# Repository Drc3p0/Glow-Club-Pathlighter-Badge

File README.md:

<div id="top"></div>

<br />
<div align="center">

<h3 align="center">Glow Club Pathlighter Badge</h3>

  <p align="center">
    wearable PCB art for the community
  
  </p>
</div>

<!-- ABOUT THE PROJECT -->
## About The Project
This PCB was created as a workshop aid to teach people about LEDs and soldering, and as a way to demistify the process of importing custom art layers into Kicad.  The PCB is intended to be worn on a lanyard, as a way to keep us all glowing safely at night. It was debuted at SOAK '22 for the There U Glow electronics education camp, used for a soldering workshop for ToorCamp 2022 participants, and at Chaos Communication Camp '23. 

### Created With

* [Procreate](https://procreate.art/)
* [Affinity Designer](https://affinity.serif.com/)
* [Kicad 6.0](https://kicad.org/)
* [OshPark](https://oshpark.com/)

The designs are free to be modified however you'd like.  

<div align="center">
  
</div>

### Build it! 

Components are easy to source and assemble, and consist of a [generic AAA single battery holder x2](https://www.mouser.com/ProductDetail/12BH412-GR), your favorite 5mm LEDs (we like these [color changing ones](https://www.amazon.com/Multicolor-Flashing-Changing-Electronics-Components/dp/B01C19END2/ref=sr_1_13?crid=3ENC4HC6ILEX9&keywords=slow+flash+led+5mm&qid=1654971525&sprefix=slow+flash+led+5mm%2Caps%2C144&sr=8-13)), and this
[tiny SPDT switch](https://www.mouser.com/ProductDetail/642-MHSS1105) to conserve your battery power.

## Contributing

Contributions are what make the open source community such an amazing place to learn, inspire, and create. Any contributions you make are **greatly appreciated**.

If you have a suggestion that would make this better, please fork the repo and create a pull request. You can also simply open an issue with the tag "enhancement".
Don't forget to give the project a star! Thanks again!

1. Fork the Project
2. Create your Feature Branch (`git checkout -b feature/AmazingFeature`)
3. Commit your Changes (`git commit -m 'Add some AmazingFeature'`)
4. Push to the Branch (`git push origin feature/AmazingFeature`)
5. Open a Pull Request

## License

Distributed under the CERN Open Hardware License (CERN-OHL-W). See `LICENSE.txt` for more information.

## Contact

For inquiries, email me @ [GlowClub@DarcyNeal.com](mailto:glowclub@darcyneal.com)

Project Link: [https://github.com/Drc3p0/Glowbug-Club-PCB](https://github.com/Drc3p0/Glow-Club-Pathlighter-Badge)

<!-- ACKNOWLEDGMENTS -->
## Acknowledgments
Thanks to:
* [OshPark](https://oshpark.org) for providing the PCBs for this community project
* the elusive Josh for providing power consumption data
* there U glow camp @ [SOAK](https://soakpdx.com/) for helping distribute these boards & [teach folks about LEDs](https://docs.google.com/document/d/180WD4LogMjx8FmKcFc0dmlTEKJ1Xa7dIHlEhSLMOAxA/edit?usp=sharing)
* [Toorcamp 2022](https://talks.toorcon.net/toorcamp-2020-2019/talk/DNWBQS/).  Over 75 students were able to assemble badges during the ~2 hr workshop.
* [Chaos Communication Camp '23 and the Hardware Hacking Village](https://events.ccc.de/camp/2023/hub/camp23/en/event/solder-a-pathlighter-pcb-badge-day-1/).  Over 160 students completed their badges over two workshops, each ~1.5hrs. 
<p align="right">(<a href="#top">back to top</a>)</p>

To date, the Glow Club now has over 450 members! May we all shine a little brighter as a result. :)

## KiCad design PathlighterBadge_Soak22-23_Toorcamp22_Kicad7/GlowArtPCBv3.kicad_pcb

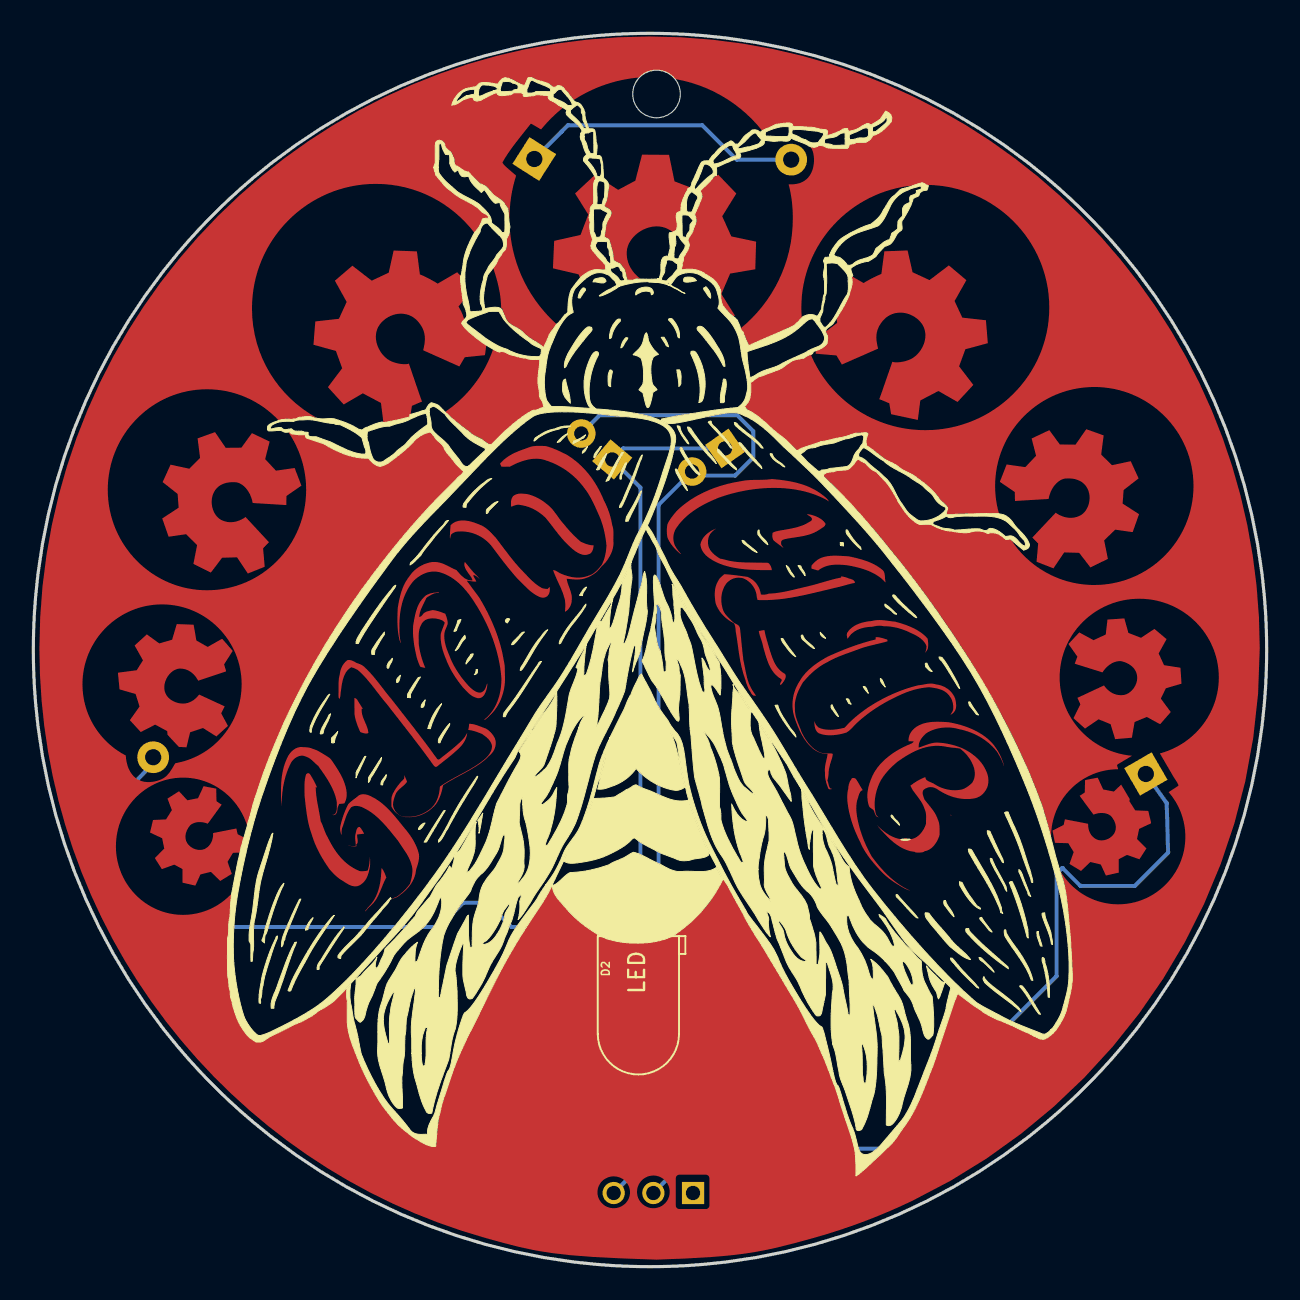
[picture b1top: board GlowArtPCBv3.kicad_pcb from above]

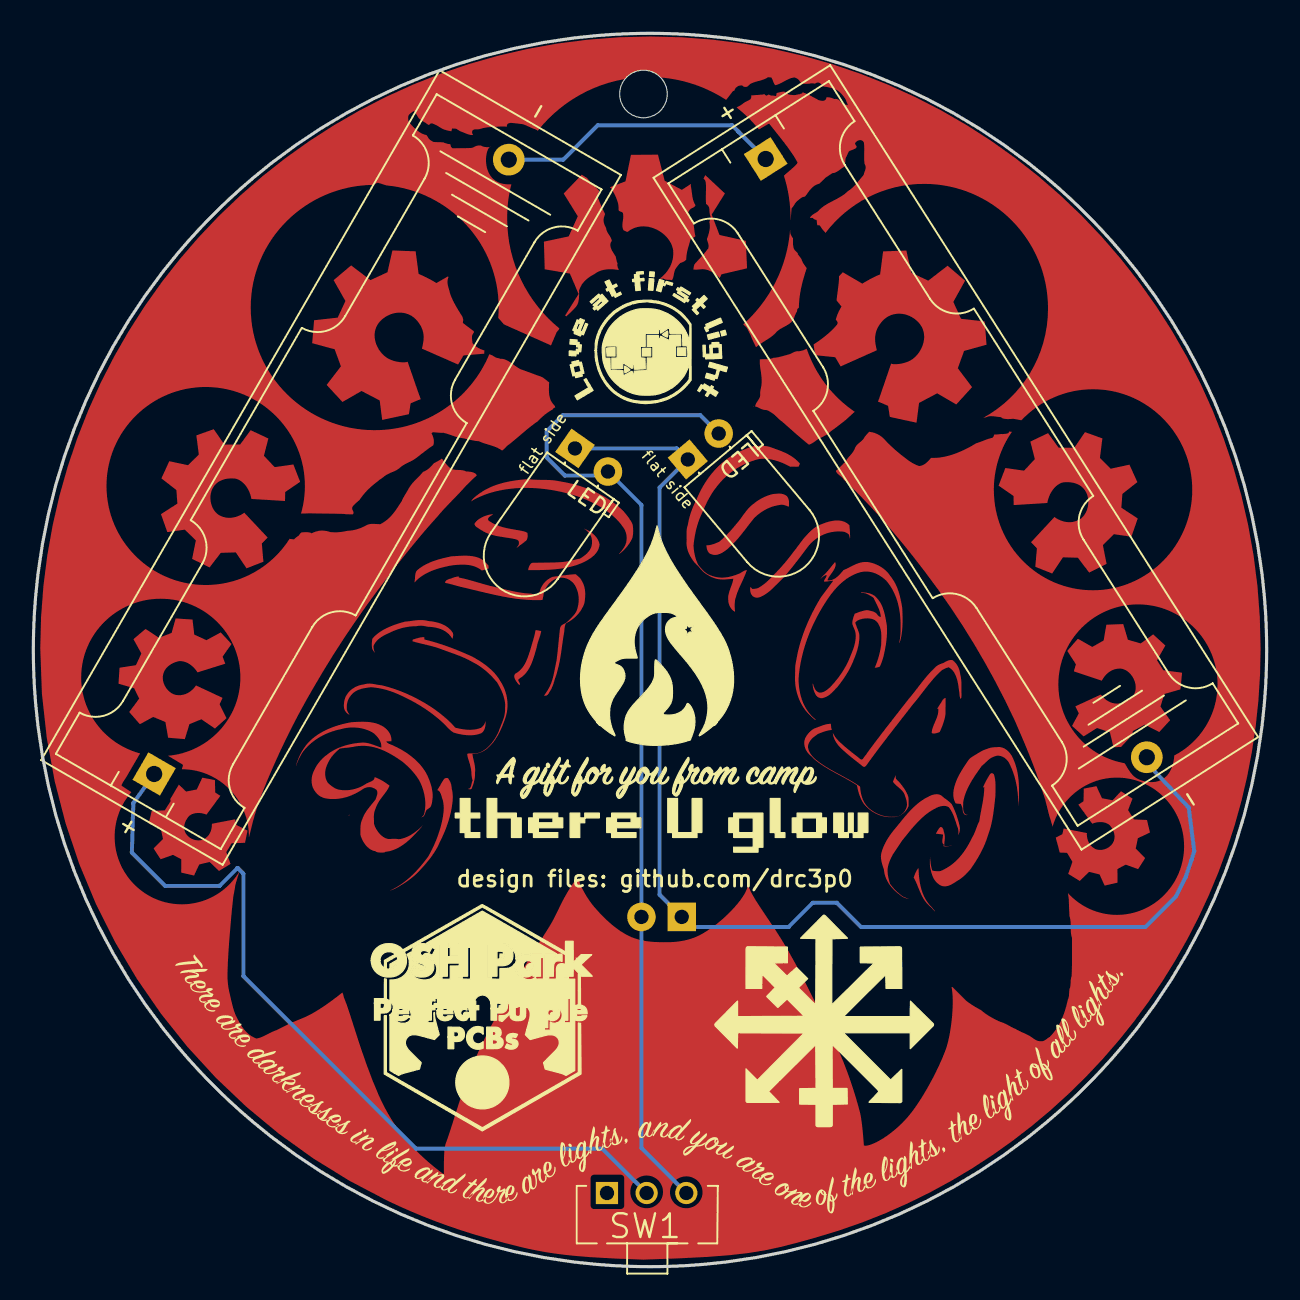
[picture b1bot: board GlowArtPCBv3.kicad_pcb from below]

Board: 2 copper layers, 77.7 x 77.7 mm, 6 parts (5 on the bottom side), 4 nets.

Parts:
BT1, BT2: AAA battery; BatteryHolder_Keystone_2466_1xAAA
D2: LED; LED_D5.0mm_Horizontal_O1.27mm_Z3.0mm
SW1: SW_SPDT; SW_MHSS1105_SPST_Angled
flat side: LED; LED_D5.0mm_Horizontal_O1.27mm_Z3.0mm
flat side#2: LED; LED_D5.0mm_Horizontal_O1.27mm_Z3.0mm

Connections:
unnamed: BT1.1 (+), BT2.2 (-)
unnamed: BT1.2 (-), D2.1 (K), flat side.1 (K), flat side#2.1 (K)
unnamed: BT2.1 (+), SW1.2 (B)
unnamed: D2.2 (A), SW1.3 (C), flat side.2 (A), flat side#2.2 (A)

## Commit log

2024-05-18 image edits
